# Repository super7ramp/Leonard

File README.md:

# Project Leonard: Indoor Guiding Drone

Upset about being lost in a new building? Feeling the urge to reach a specific room but you do not want to get lost? It seems like you need the help of our guiding drone!

We are proud to introduce to you are newest product: **Findy**! **Findy** is a completely autonomous drone acting inside of buildings. Thanks to Bluetooth beacons deployed in all of the building, the drone is able to calculate his position and define paths to get to any equipped room or hallway!

Why would I choose Findy, you may ask? Maybe you do not understand how to read a map. And well, who bring a map when he goes to the mall? 

## Features

Here are the mains features of **Findy**:
* Autonomous flight: flight controls are designed with [SCADE Suite®](http://www.systerel.fr/).
* Guiding procedure: **Findy** is able to choose the shortest path to reach a specific destination. All you have to do is to tell him where you want to go.
* Drone location retrieving: you are able to get the drone position at any time (pc application).
* Remote control with Android application (not implemented yet, for now there is a small pc application)
* Definition of meeting point (not implemented yet)

For more details, please visit [our website](https://sites.google.com/site/projetsecinsa/projets-2015-2016/project-leonard).

## Get it started

There are two programs:
* One embedded on the drone, which controls the drone movements.
* One running on a computer, which communicates with the drone.

The procedure described here has been tested on Linux, you'll have to adjust it if you want to use other platforms.

### Compilation

You need a cross-compiler in order to compile the embedded program (drone side).

If you use Ubuntu, you can use the ARM cross-compiler from the repositories.
```bash
 $ sudo apt-get install gcc-arm-linux-gnueabi
```

Note: You can use other cross-compilers, just edit the `CC` variable in the Makefile.

Once you have installed the cross-compiler, you just have to run the Makefile.
```bash
 $ make
```

The generated program is named `Control_Law.elf`.

The user program (pc side) needs to be compiled separately:
```bash
 $ cd src/user_app
 $ make
```

The Makefile in `src/user_app` defines GCC as compiler, just change the `CC` variable if you want to use something else.
The generated program is named `Findy`.

### Installation

#### Drone

##### Drone hardware

In order to make the drone detect the beacons, you need to plug the BLE Nano under the drone, on the available Serial pins. The Ble Nano takes his power from the drone too. The BLE Nano is mounted on a board which has to be connected respecting the following schematic:

##### Drone software

The drone program is an ARM executable, therefore designed to be runned on the drone.

To send it on the drone you need to...
1. Power on the drone
2. Connect by Wifi to the drone
3. Put the executable with ftp:
```bash
 $ ftp 192.168.1.1
 ftp> put Control_Law.elf
```

It will be send in the `/data/video` folder of the drone filesystem.

Also, the drone uses a predefined map of the room to locate itself and compute the paths to the given destination. Therefore, the map needs to be adapted to the test room.

The map is written in a simple text format. You’ll find a description of the format in `src/shortest_path/map_format.md`, examples in `src/shortest_path/examples`, and scripts to help you to create and visualize your map in `src/shortest_path/scripts`.

Once your map is ready, you’ll have to rename it `demo_map` and install it on the drone:
```bash
 $ ftp 192.168.1.1
 ftp> put demo_map
```

**Warning:** in this first release, the bluetooth beacons position and geolocation parameters are hardcoded. Therefore you’ll need to edit `src/uart/parser.c` in addition to your map file and rebuild the project.

#### Beacons software

To flash a new program you need a CC debugger and the Bluegiga SDK (available on their website, you need to create an account).
You can refer to datasheet and user application provided in the github to write your own program. Once you have written your script, you need to plug the beacon following this schematic :

Open the “BLE Update Tool” that you can found in the SDK folder. Make sure that the CC debugger is well detect clicking on “Refresh”. Push the button on the CC debugger and make sure the led is green (if not, make sure you have plug correctly the CC debugger and the the beacon is switched on). Click on “Info” : the tool should provide you information about the BLE112 module embedded on the drone. Click on “Browse” and fin your .bgproj file. You can now click on “Update” to update your beacon firmware.

#### User application

The pc application is a standalone executable, it can be launched from anywhere so you can install it wherever you want.

### Use

First, deploy the beacons in the room. Once is done, you can switch on the drone.

**Warning:** In this first release, the magnetometer control is not as robust as it should. Make sure to positionate your drone’s head approximately 90° counterclockwise from the north before starting the executable, in order to be sure that the calibration goes well.

There is no daemon to start our drone program so you’ll have to connect to the drone with telnet in order to launch it.
```
 $ telnet 192.168.1.1
 # cd /data/video/
 # ./Control_Law.elf
```

Once the drone program is launched, you can launch the user application from your computer to control the drone and ask it to go to a destination.
```bash
 $ src/user_app/Findy
```

If you have connection issues:
* Make sure you’re connected by Wifi to the drone and that there is no other devices connected by wifi to the drone.
* Disable your firewall (the drone will try to connect to your device).

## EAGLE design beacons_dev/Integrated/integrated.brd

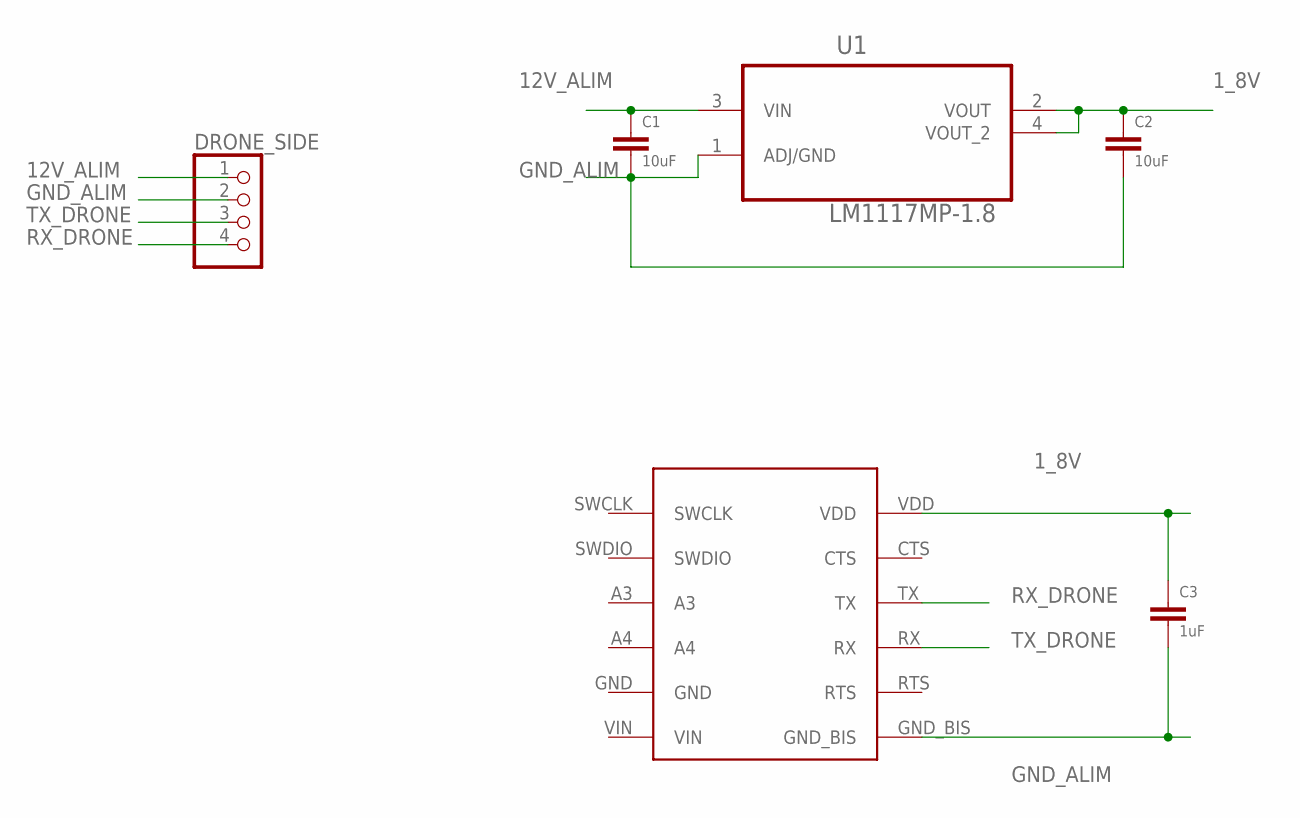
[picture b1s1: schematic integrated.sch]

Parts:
C1, C2: 10uF; R0805
C3: 1uF; R1206
DRONE_SIDE: PINHD-1X4; 1X04
U1: LM1117MP-1.8; SOT230P696X180-4N
U$2: BLE_NANO; MOUNTED_ON_PINHEADS

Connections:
1_8V: C2.1, C3.1, U1.2 (VOUT), U1.4 (VOUT_2), U$2.VDD
12V_ALIM: C1.1, DRONE_SIDE.1, U1.3 (VIN)
GND_ALIM: C1.2, C2.2, C3.2, DRONE_SIDE.2, U1.1 (ADJ/GND), U$2.GND_BIS
RX_DRONE: DRONE_SIDE.4, U$2.TX
TX_DRONE: DRONE_SIDE.3, U$2.RX

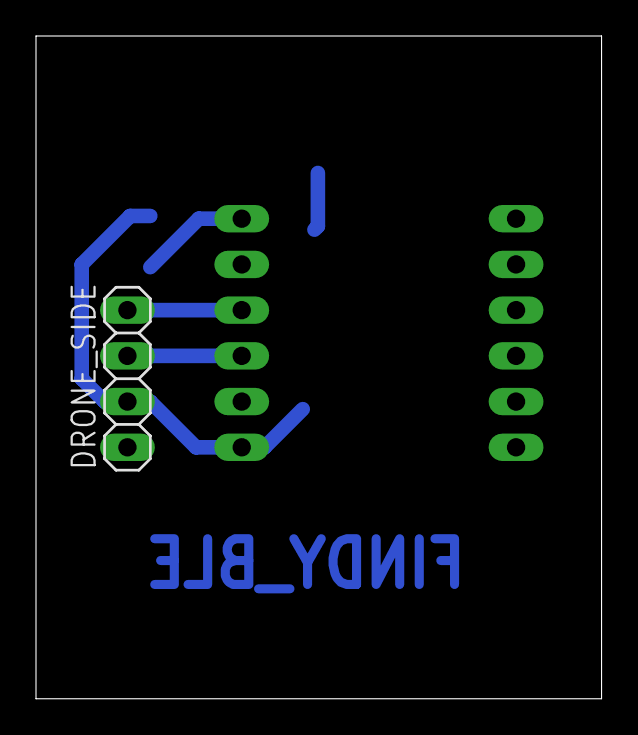
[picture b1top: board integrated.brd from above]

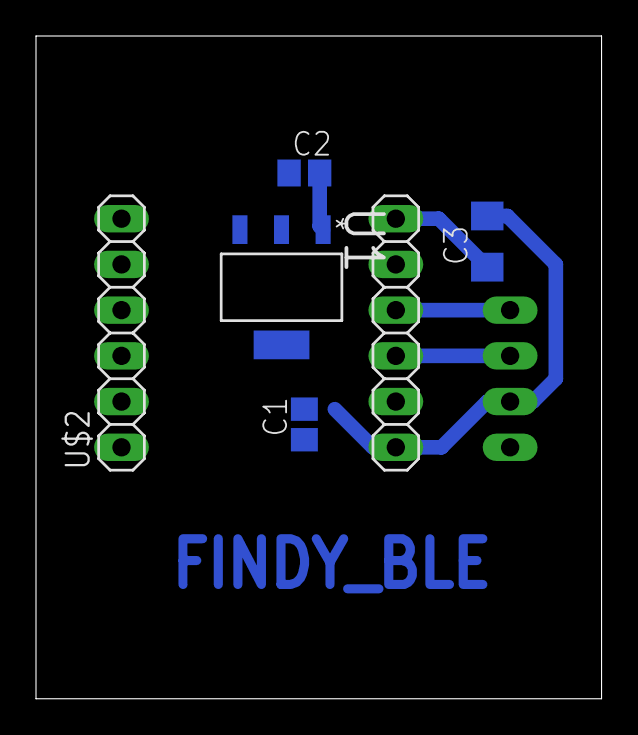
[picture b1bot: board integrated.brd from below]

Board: 2 copper layers, 31.4 x 36.8 mm, 6 parts (5 on the bottom side), 5 nets.

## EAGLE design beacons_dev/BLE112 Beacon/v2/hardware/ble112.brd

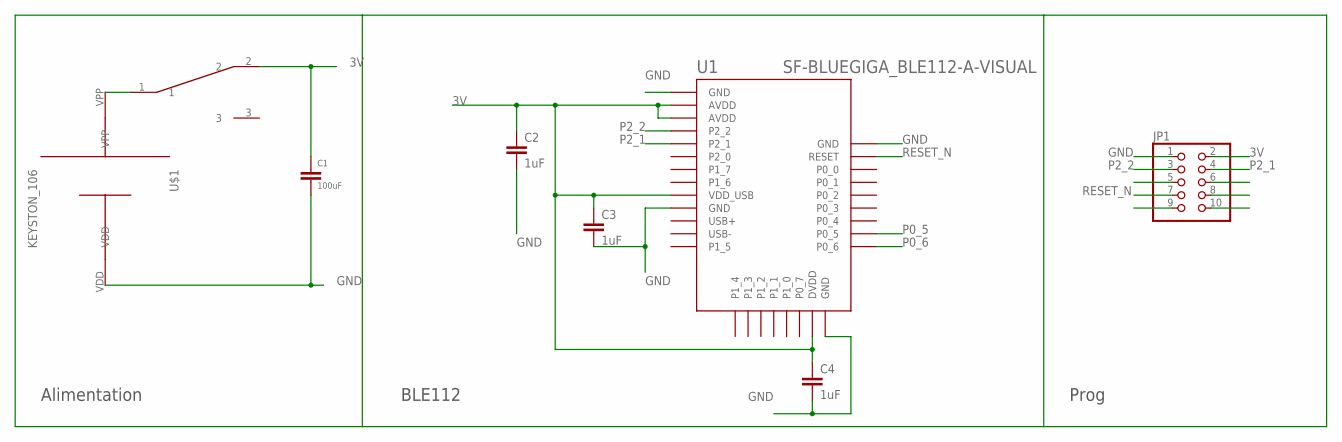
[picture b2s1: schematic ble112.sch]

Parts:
C1: 100uF; R1206
C2, C3, C4: 1uF; C1210
JP1: PINHD-2X5; 2X05
U1: SF-BLUEGIGA_BLE112-A-VISUAL; SF-BLUEGIGA_BLE112-A
U$1: KEYSTON_106; CELL_HOLDER_PACKAGE
U$2: 1K2; 1X03/90

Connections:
3V: C1.1, C2.1, C3.1, C4.1, JP1.2, U1.AVDD1 (AVDD), U1.AVDD2 (AVDD), U1.DVDD, U1.VDD_USB, U$2.2
CELL_VOLTAGE: U$1.VPP, U$2.1
GND: C1.2, C2.2, C3.2, C4.2, JP1.1, U1.GND1 (GND), U1.GND2 (GND), U1.GND3 (GND), U1.GND4 (GND), U$1.VDD
P0_5: U1.P0_5
P0_6: U1.P0_6
P2_1: JP1.4, U1.P2_1
P2_2: JP1.3, U1.P2_2
RESET_N: JP1.7, U1.RESET

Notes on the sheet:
Alimentation
BLE112
Prog

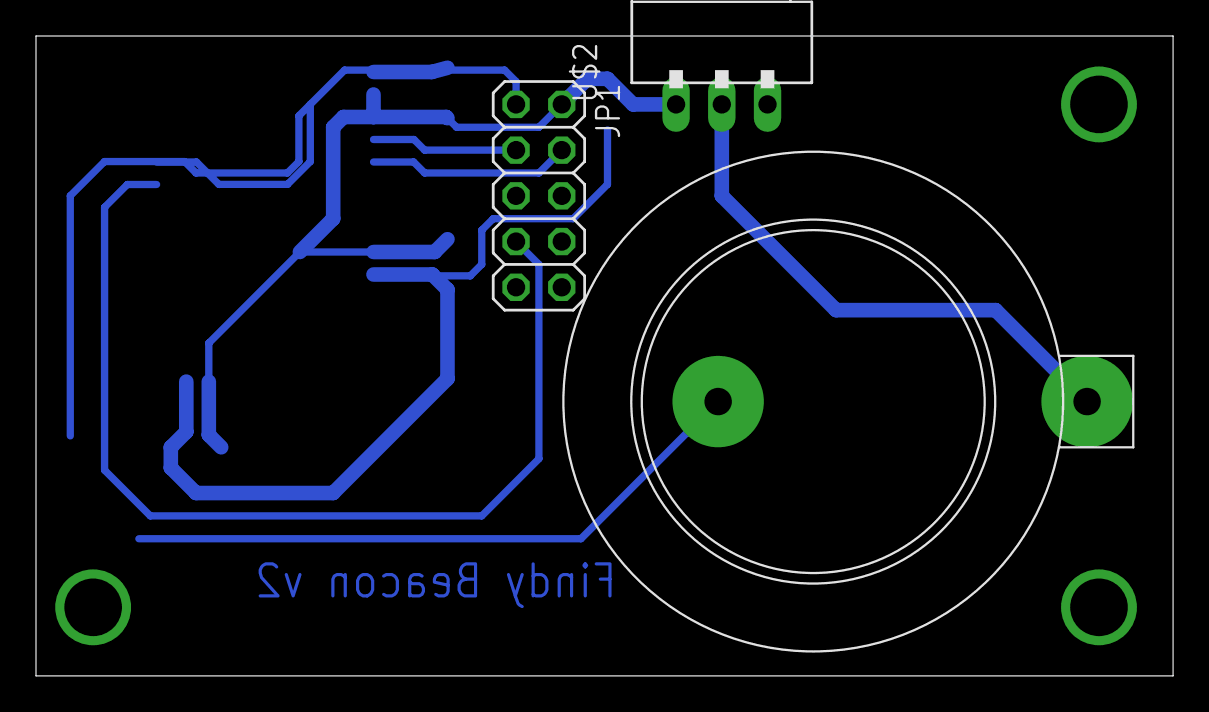
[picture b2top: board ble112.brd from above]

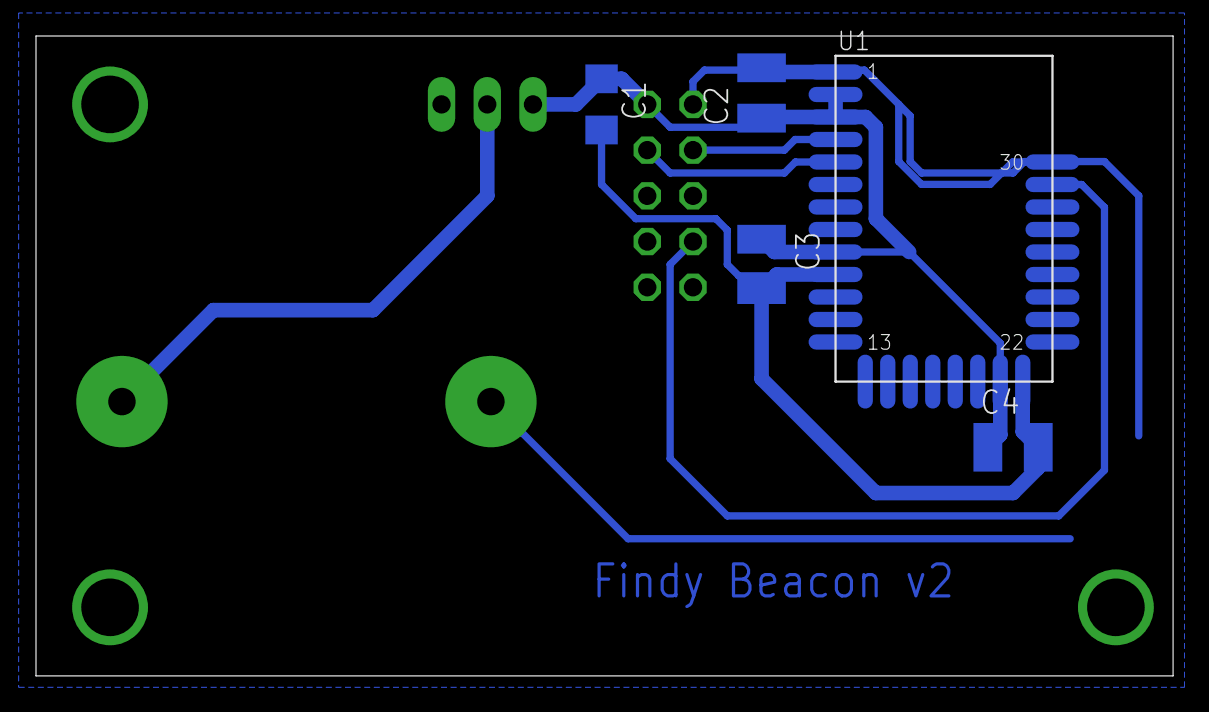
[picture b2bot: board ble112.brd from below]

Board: 2 copper layers, 63.2 x 35.5 mm, 8 parts (5 on the bottom side), 6 nets.

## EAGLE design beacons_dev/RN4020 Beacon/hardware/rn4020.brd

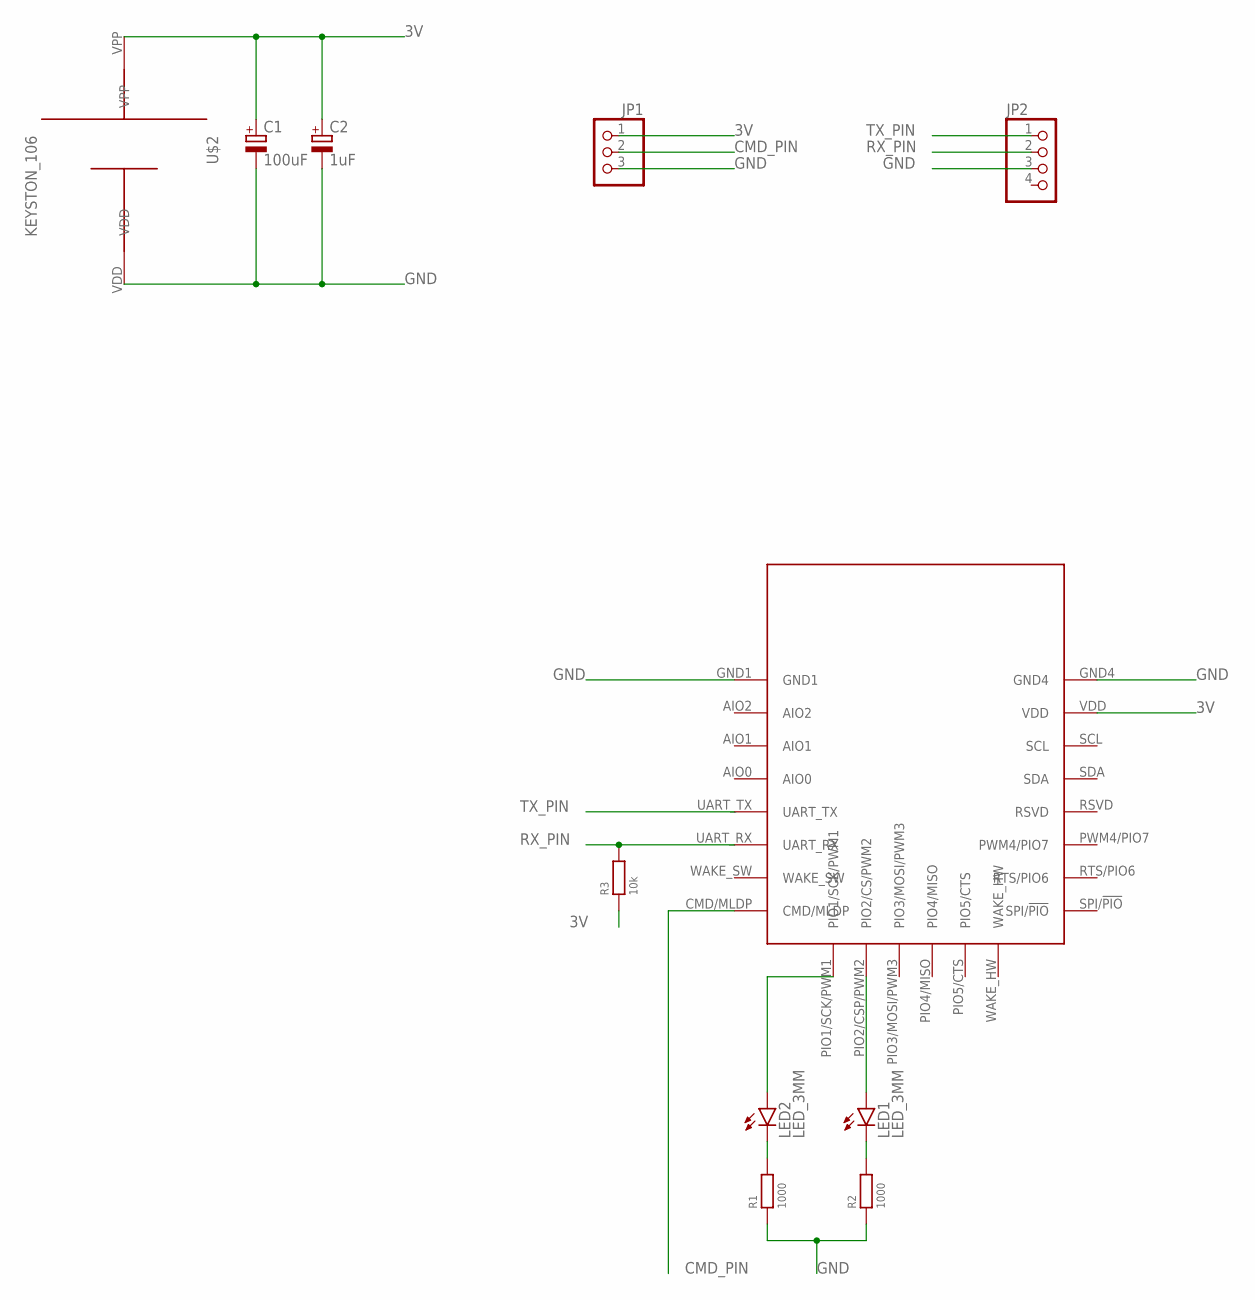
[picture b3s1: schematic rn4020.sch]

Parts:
C1: 100uF; E2,5-6
C2: 1uF; E2,5-7
JP1: PINHD-1X3; 1X03
JP2: PINHD-1X4; 1X04
LED1, LED2: LED_3MM; LED3MM
R1, R2: 1000; 0207/10
R3: 10k; 0207/10
U$1: RN_4020; RN4020
U$2: KEYSTON_106; CELL_HOLDER_PACKAGE

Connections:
3V: C1.+, C2.+, JP1.1, R3.1, U$1.VDD, U$2.VPP
CMD_PIN: JP1.2, U$1.CMD/MLDP
GND: C1.-, C2.-, JP1.3, JP2.3, R1.1, R2.1, U$1.GND1, U$1.GND4, U$2.VDD
unnamed: LED2.A, U$1.PIO1/SCK/PWM1
unnamed: LED1.A, U$1.PIO2/CSP/PWM2 (PIO2/CS/PWM2)
unnamed: LED1.K (C), R2.2
unnamed: LED2.K (C), R1.2
RX_PIN: JP2.2, R3.2, U$1.UART_RX
TX_PIN: JP2.1, U$1.UART_TX

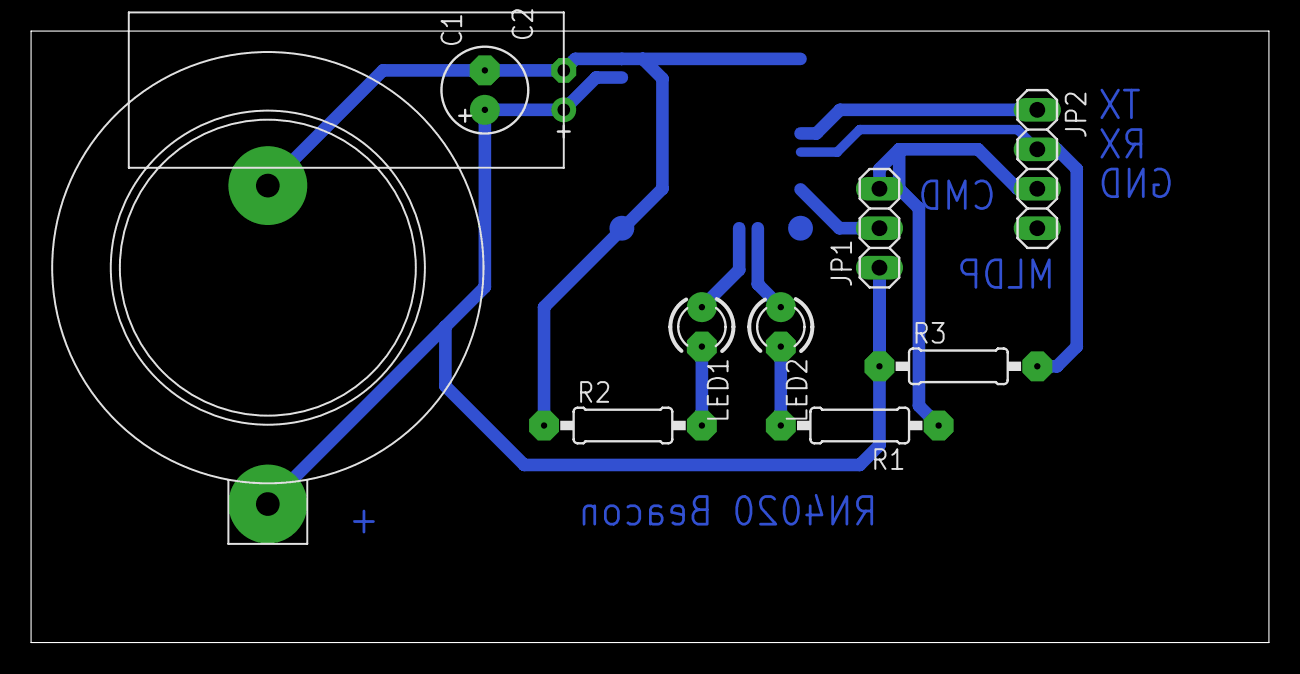
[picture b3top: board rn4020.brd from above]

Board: 2 copper layers, 79.7 x 39.4 mm, 11 parts (1 on the bottom side), 9 nets.

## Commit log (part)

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2015-10-28 [doc] Add environment setup instructions Cross-compiling instructions not complete yet, will come soon
2015-10-28 [src] Add fix-sdk-examples-build-patch Just run "patch -p1 < fix-sdk-examples-build.patch" from the root SDK directory to fix some build errors.
2015-10-28 [doc] Fix title sizes in environment-setup.fr.md
2015-10-29 [doc] Add cross-compilation instructions
2015-10-29 [doc] Fix typo
2015-10-29 [doc] Add specific instructions for codesourcery
2015-11-02 Add reference to the SCADE suite.
2015-11-06 Add a test program: sending AT command to the drone
2015-11-10 Add functions to create at-commands
2015-11-11 Add some missing const
2015-11-11 Add send function
2015-11-11 Add watchdog reset command
2015-11-11 Add floating point conversion
2015-11-11 Add file message_drone: functions which use at-command functions in order to create easily a command and send it on UDP port (using send_message() function). send_message() is commented now in order 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
2015-11-13 modif files: message_drone / at-commands / common / sender / test-at-commands
2015-11-13 Add files: programs which do a trip to the drone takeoff and land / takeoff-straight line-land (go_findy) / takeoff-rotation-land / takeoff-roundtrip-land
2015-11-17 [ADD] : beacons development files
2015-11-17 Create a close_socket function instead of using an extern socket id
2015-11-17 Don't return an error on make clean if the build folder doesn't exist
2015-11-17 Add headers
2015-11-17 Add LICENSE file
2015-11-17 Remove test_at
2015-11-17 Add Doxyfile and integrate it in the Makefile Just use 'make doc' to generate an HTML documentation
2015-11-17 [ADD] : Procedure tests pour directivité
2015-11-19 Add FindyApp
2015-11-21 Improved matlab script and did some measurements
2015-11-22 NEw version of beacon with BLE112
2015-11-24 Modif error in set_gaz() function
2015-11-24 Add files spoofer
2015-11-24 Add test_pcap.c
2015-11-24 Add files: navdata_controller.c / navdata_controller.h modif: initialize_socket() function in sender, so modif in all demonstration files
2015-11-25 add state machine
2015-11-25 Add Adrien's work on navdata
2015-11-25 Add libpcap headers and the cross-compiled library
2015-11-25 Rework sender in order to be able to create several sockets
2015-11-26 Add uart program
2015-11-26 Fix mutex_unlock position
2015-11-26 Various changes related to navdata Bootstrap phase seems ok now but it doesn't work after that
2015-11-26 Some modifications, but the navdata just doesn't move... We do receive them, there is a sequence number which is incremented but the rest just doesn't move...
2015-11-26 Updated beacon design and added raw localization demo with Matlab
2015-11-26 Updated raw localization demo
2015-11-27 update uart
2015-11-27 Some additions to test acknowledgment bit Still doesn't work, working with tcpdump to try to find out what is going on
2015-11-27 Still not working, navdata.header is ok but navdata.demo isn't There is something wrong the two
2015-11-28 Got it. sizeof() on the wrong type. TODO: more tests and cleanup
2015-11-28 state_machine OK for the moment
2015-11-28 Add magneto calibration command
2015-11-28 Some cleanup
2015-11-28 Fix indentation
2015-12-05 [map] Add functions to read a map and fill a graph structure (T48) TODO See with Adrien if the structures are OK for him
2015-12-05 Update map_format.md (T48)
2015-12-06 Add weight attribute to adjacency list
2015-12-06 Add a common file for shared map structures
2015-12-06 [Dijkstra] Review and integration with map_reader - modified shortest_path.{c,h} to use structures from map_common.h (just renamed element_t into adjacency_list_t actually and use the graph_t structu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
2015-12-07 Added first version of BT integration T32-0 T50-0 T33-0
2015-12-07 add parser program
2015-12-08 SCADE IMPLEMENTATION
2015-12-08 [map] Add scripts to export and display maps
2015-12-09 Remove file *.o and *~
2015-12-09 [navdata] Fix magneto range
2015-12-09 [tests] Fix compilation instructions
2015-12-09 Edit parser.* and makefile
2015-12-09 Edit parser.c
2015-12-09 Add localisation
2015-12-09 [map] Add grid map generator A script which generates a grid of nodes
2015-12-09 [map] Don't display empty adjacency list In case there is only one node
2015-12-11 [map] Add more paths to gridmap and some examples
2015-12-11 Update Localisation and reception
2015-12-11 Added functionnal serial code T60-0
2015-12-11 Update ttl function
2015-12-13 Added complete demo for bluetooth integration with beaocn A & beaocn B T36-0
2015-12-13 Update Localisation
2015-12-13 [dijkstra] Don't use == to compare two floats ... because there are always small errors in floating-point calculations. Use a comparison with a threshold instead
2015-12-14 Localisation
2015-12-14 update control law
2015-12-17 [ADD] Beacon detection on drone, the drone update a visible beacon tab T65-0 T66-0
2015-12-18 integration of dijkstra function in controlTask
2015-12-19 add some fontions in control_task (break, zip piece of code in fonction)
2015-12-19 Add sockte com
2015-12-28 [ADD] Position computation on drone. Not fully tested, need a room bigger than student appartment to deploy all beacons T63-0 T77-0 T78-0 T81-0
2015-12-28 [ADD] Added missing files localisation.c and localisation.h T63-0 T77-0 T78-0 T81-0
2015-12-29 add pcCom and params
2015-12-29 Update socket sender and receiver
2015-12-31 user can send order to the drone and close socket
2016-01-03 Added first version of location weighted computation. Removed "Detected Location" from saved information. Fixed getIndexOfCloserBeaconissue with return type T86-0 T83-0
2016-01-04 update pcCom
2016-01-04 ADD : function to print position on a map in console T88-0
2016-01-04 [map] Adjust map2dot when there is a lot of nodes
2016-01-04 [map] Add example files
2016-01-04 [map] Remove old examples
2016-01-04 Fixed buggy map display
2016-01-04 insert dijkstra and modif controltask
2016-01-04 [doc] Add design file (wip)
2016-01-04 Fixed wrong variable types in position computation
2016-01-04 [ADD] 3D file of beacon support T90-0
2016-01-04 Unified number of visible detection code. Protected computation from bad rssi values T94-0 T87-0
2016-01-05 Added position filtering (done by meaning values) T93-0. Added check for valid computed position to exclude Nan values. Has to be reworked T91-0
2016-01-06 Added Bluetooth processing in corresponding THREAD T95-0
2016-01-07 Fixed Bluetooth Thread
2016-01-07 Added some debug print for bluetooth localisation
2016-01-07 clean com folder
2016-01-07 Modification control_com, add variable for sending and receiving message
2016-01-07 Modification of state machine programme for sending and receiving message form pc
2016-01-07 Update script state machine
2016-01-07 Changed a few things for testing purpose
2016-01-07 Update state machine and bluetooth code Stack mashing problem still pending
2016-01-07 [bluetooth] Fix beacon G
2016-01-07 [Bluetooth] Added pthread to allow mutex usage in bluetooth. Corrected debug display
2016-01-07 [map] Add script to rotate map
2016-01-08 new file
2016-01-09 add fonction in calcul
2016-01-09 new fonction
2016-01-09 beginning of search for the closest departure point
2016-01-09 update controltask
2016-01-09 [shortest path] Decrease ERROR_COORD
2016-01-09 [movement] Fix indentation and comment some printfs
2016-01-09 [controlTask] Various changes, bluetooth reads disabled for now
2016-01-10 Separated some debug output in proper functions. Modified location parameters to improve stability
2016-01-10 Reorganized proper code architecture (each layer is only dependant of lower layers). Added proper makefile T102-0 T106-0
2016-01-10 [Bluetooth geolocation] Improved position filtering by changing number of recorded position used in mean following number of visible beacon. Fix wrong rssi read T104-0
2016-01-10 [Bluetooth] Changed location parameters to make the position more stable
2016-01-11 new for comm
2016-01-11 Update params
2016-01-11 Update display position drone
2016-01-11 Add a simulated bluetooth thread
2016-01-11 Move simulated_bluetooth.* tp bluetooth_com.* and backup bluetooth_com.* in bluetooth_com.original.*
2016-01-11 Uncomment read_data in controlTask
2016-01-11 Fix include in bluetooth_com.c
2016-01-11 Add missing structure, sorry
2016-01-11 new com
2016-01-11 Update display menu
2016-01-11 Modification display menu
2016-01-11 [Bluetooth] Adapted display for showcase
2016-01-13 [State Machine] Replaced sprint review demo with fictive data by the real thread (no .c extension to allow use of Makefile without compiling the demo)
2016-01-13 [State machine] Renamed sprint review demo bluetooth thread
2016-01-13 [Map] Added makefile to generate obj files
2016-01-13 [Cleanup] Rearranging source directory
2016-01-13 [Cleanup] Almost rearranged the whole source directory, only doubt about sender.c & sender.h remaining
2016-01-13 [Cleanup] All source files are now in specific directories.
2016-01-14 [Cleanup] all files are reorganised. All makefiles are wrote but thre is still an issue with the ./src/com building. The old ugly way (withsh script) still work
2016-01-14 [makefile] Add arch variable
2016-01-14 [tests] Comment unimplemented function
2016-01-14 [Makefile] Just fix it
2016-01-14 [navdata] Comment unneeded printf
2016-01-14 Update Makefile
2016-01-14 [Cleanu] Main Makefile operational
2016-01-14 [Cleanup] Removed ugly building script
2016-01-14 [Bluetooth] Removed gatt files
2016-01-16 [control] Wait for bluetooth data sabilization in mission loop (WIP)
2016-01-18 [controlTask] Create rotate_to_desired_angle function
2016-01-18 Update display langage
2016-01-18 [control] Add moveto function
2016-01-19 [control] Modify printf
2016-01-19 [shortest_path] Cost must be float, not an int! Because the path weights are floats, not int.
2016-01-19 Updated Makefiles to fix com issues. Deletes ugly building script T113-0
2016-01-19 [control] Be more strict on findy_lost The drone now recalculates its cap after it detects it doesn't go closer to the destination after a move.
2016-01-19 [Diagnostic] Added signal capture
2016-01-19 [Cleanup] Added app rule in general makefile
2016-01-20 [control] Rewrite mission part in controlTask
2016-01-20 [command] Don't set the progressive flag on gaz Since we want to move only vertically
2016-01-21 [shortest_path] Increase ERROR_COORD There will be overlap though, but it avoids to have blank spaces
2016-01-21 [control] Add ARRIVED state in mission + pass current position point to move_to functions + don't turn towards North at the beginning (short-circuit computeOffsetMag)
2016-01-23 [mission] Check if the destination point is valid
2016-01-23 [com] Add an ugly IP address detection Because the first connected machine is not necessarily 192.168.1.2
2016-01-23 [com] Fix ip detection command
2016-01-24 [com] Fix memory leak
2016-01-24 [com] Fix indentation
2016-01-24 [com] Don't go crazy if the pc app closes * Check the return value of tcp read for end-of-file (disconnection) * Add SO_REUSEADDR option to the listener socket in order to be able to restart it immed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
2016-01-24 [com] Fix wrong offstet of 1 in substring function
2016-01-25 sending bluetooth data
2016-01-25 stop the mission when the pc asks it
2016-01-25 [com] Fix typo
2016-01-25 [com] Comment printf to clean the display
2016-01-25 [pc app] Change available positions + decrease refreshing time for drone live coordinates
2016-01-25 [movement] Uncomment computeOffsetMag
2016-01-25 [com] Send live coordinates to pc app + remove unnecessary printfs
2016-01-25 [control] Last updates + sleep(1) after rotation in order to stabilize the drone + change speed of movements + land when mission ends + ...
2016-01-25 [control_com] Add missing actions Not tested! To revert if it breaks something.
2016-01-27 add orders in control_com
2016-01-27 [README] Improve the readme (WIP)
2016-01-27 [README] Improve the readme (WIP): compilation
2016-01-27 [README] Improve README (WIP): use on Linux
2016-01-27 [README] Improve README (WIP)
2016-01-27 [README] Fix ordered list
2016-01-27 [README] Prompts
2016-01-27 [Clean Up] COmpleted Readme procedure to build the project
2016-01-27 Modified captures directory
2016-01-27 Update README.md
    Fix typo
